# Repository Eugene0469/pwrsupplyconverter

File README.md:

# pwrsupplyconverter

This is a project designing a 220VAC to 28VDC power supply for a jig workstation.View Wiki for more information.

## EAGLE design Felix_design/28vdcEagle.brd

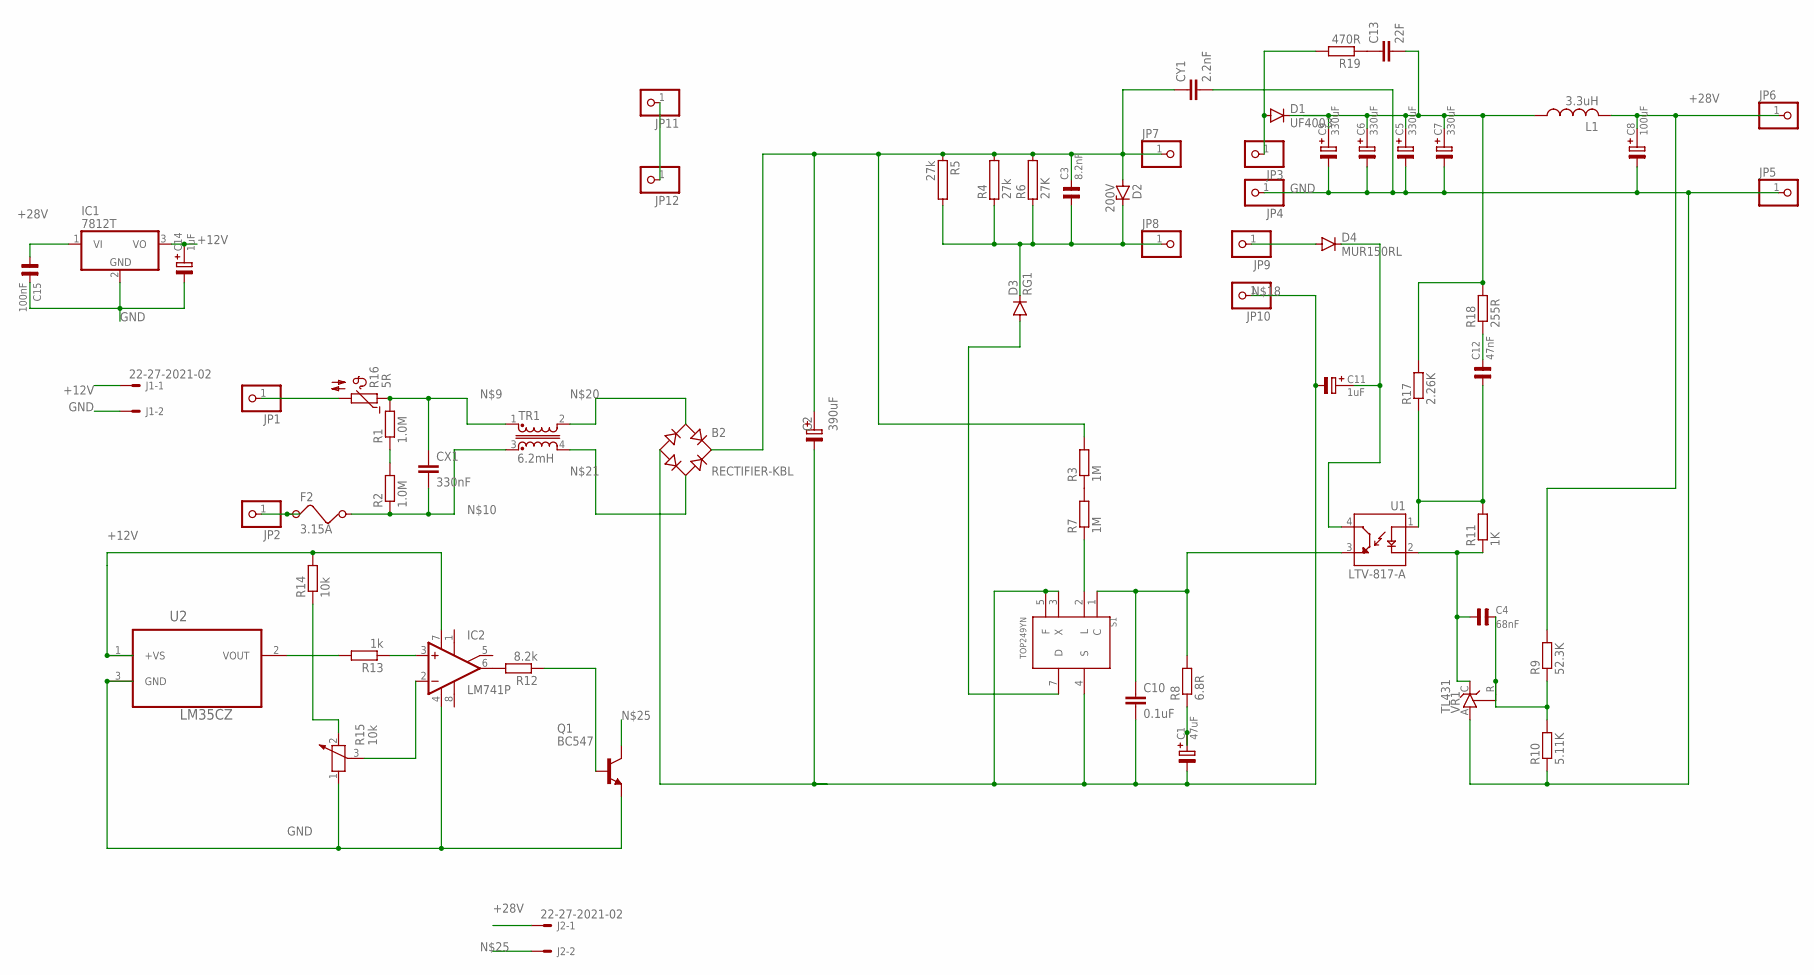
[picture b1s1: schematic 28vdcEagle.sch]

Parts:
B2: RECTIFIER-KBL; KBL
C1: 47uF; E1,0-3
C2: 390uF; E3,5-10
C3: 8.2nF; C14,5
C4: 68nF; C2,5
C5, C6, C7, C9: 330uF; E2,0-5
C8: 100uF; E2,0-5
C10: 0.1uF; C025-030X050
C11, C14: 1uF; E1,0-3
C12: 47nF; C2,5
C13: 22F; C025-030X050
C15: 100nF; C2,5
CX1: 330nF; XC15B10
CY1: 2.2nF; YC7B5
D1: UF4003; DO41-10
D2: 200V; C1702-15
D3: RG1; DO204-10
D4: MUR150RL; DO41-10
F2: 3.15A; FUSE
IC1: 7812T; TO220H
IC2: LM741P; DIL08
J1, J2: 22-27-2021-02; 6410-02
JP1, JP2, JP3, JP4, JP5, JP6, JP7, JP8, JP9, JP10, JP11, JP12: PINHD-1X1; 1X01
L1: 3.3uH; 0207/10
Q1: BC547; TO92
R1, R2: 1.0M; 0207/10
R3, R7: 1M; 0207/10
R4, R5: 27k; KP290
R6: 27K; KP290
R8: 6.8R; 0207/10
R9: 52.3K; 0207/10
R10: 5.11K; 0207/10
R11: 1K; 0207/10
R12: 8.2k; 0207/10
R13: 1k; 0207/10
R14: 10k; 0207/10
R15: 10k; PT-10
R16: 5R; B57164
R17: 2.26K; 0207/10
R18: 255R; 0207/10
R19: 470R; 0207/10
S1: TOP249YN; TO127P470X1029X2061-7P
TR1: 6.2mH; U15
U1: LTV-817-A; DIP762W50P254L510H500Q4
U2: LM35CZ; TO127P254X495-3P
VR1: TL431; TO92-CLP

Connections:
+12V: C14.+, IC1.3 (VO), IC2.7 (V+), J1.1, R14.2, U2.1 (+VS)
+28V: C8.+, C15.1, IC1.1 (VI), J2.1, JP6.1, L1.2, R9.2
GND: C5.-, C6.-, C7.-, C8.-, C9.-, C14.-, C15.2, CY1.2, IC1.2 (GND), IC2.4 (V-), J1.2, JP4.1, JP5.1, Q1.1 (E), R10.1, R15.1, U2.3 (GND), VR1.A
unnamed: R1.1, R2.2
unnamed: B2.+, C2.+, C3.2, CY1.1, D2.A, JP7.1, R3.2, R4.2, R5.1, R6.2
unnamed: C11.+, D4.C, U1.4 (CT)
unnamed: R3.1, R7.2
unnamed: R7.1, S1.2 (L)
unnamed: IC2.6 (OUT), R12.2
unnamed: D3.A, S1.7 (D)
unnamed: C3.1, D2.C, D3.C, JP8.1, R4.1, R5.2, R6.1
unnamed: CX1.1, R1.2, R16.1, TR1.1
unnamed: CX1.2, F2.2, R2.1, TR1.3
unnamed: C4.2, R9.1, R10.2, VR1.R
unnamed: C4.1, R11.1, U1.2 (C), VR1.C
unnamed: C12.1, R11.2, R17.1, U1.1 (A)
unnamed: C5.+, C6.+, C7.+, C9.+, C13.2, D1.C, L1.1, R17.2, R18.2
unnamed: JP11.1, JP12.1
unnamed: C13.1, R19.1
unnamed: C10.1, R8.2, S1.1 (C), U1.3 (ET)
unnamed: B2.-, C1.-, C2.-, C10.2, C11.-, JP10.1, S1.3 (X), S1.4 (S), S1.5 (F)
unnamed: D4.A, JP9.1
unnamed: B2.AC1, TR1.2
unnamed: B2.AC2, TR1.4
unnamed: R13.2, U2.2 (VOUT)
unnamed: Q1.2 (B), R12.1
unnamed: J2.2, Q1.3 (C)
unnamed: IC2.3 (+IN), R13.1
unnamed: JP1.1, R16.2
unnamed: R14.1, R15.2
unnamed: IC2.2 (-IN), R15.3
unnamed: C1.+, R8.1
unnamed: C12.2, R18.1
unnamed: D1.A, JP3.1, R19.2
unnamed: F2.1, JP2.1

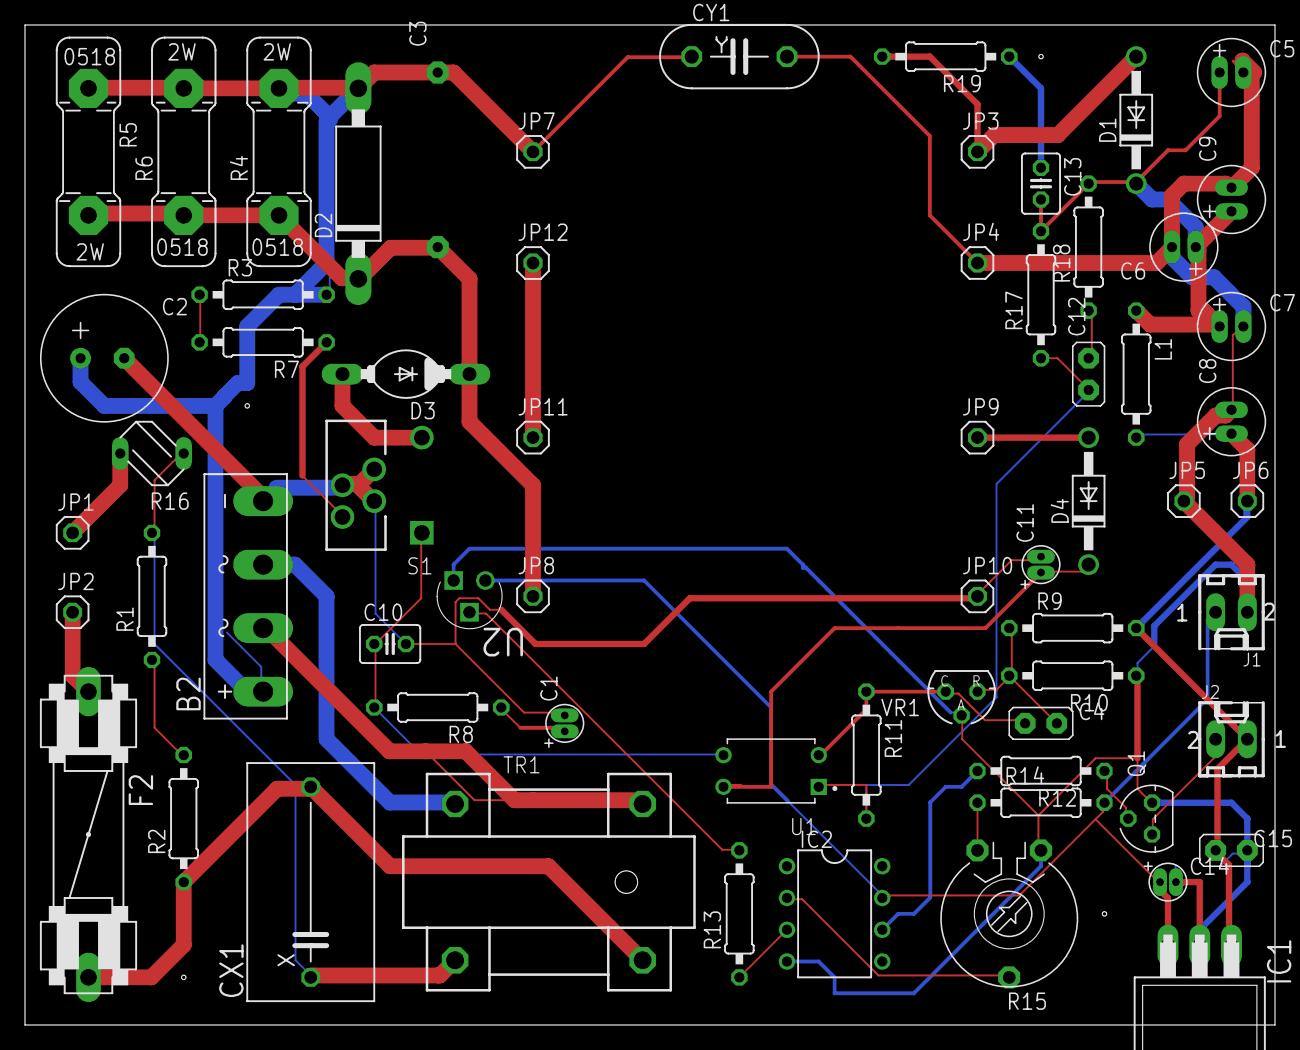
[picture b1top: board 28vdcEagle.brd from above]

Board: 2 copper layers, 100.0 x 80.0 mm, 65 parts (0 on the bottom side), 35 nets.

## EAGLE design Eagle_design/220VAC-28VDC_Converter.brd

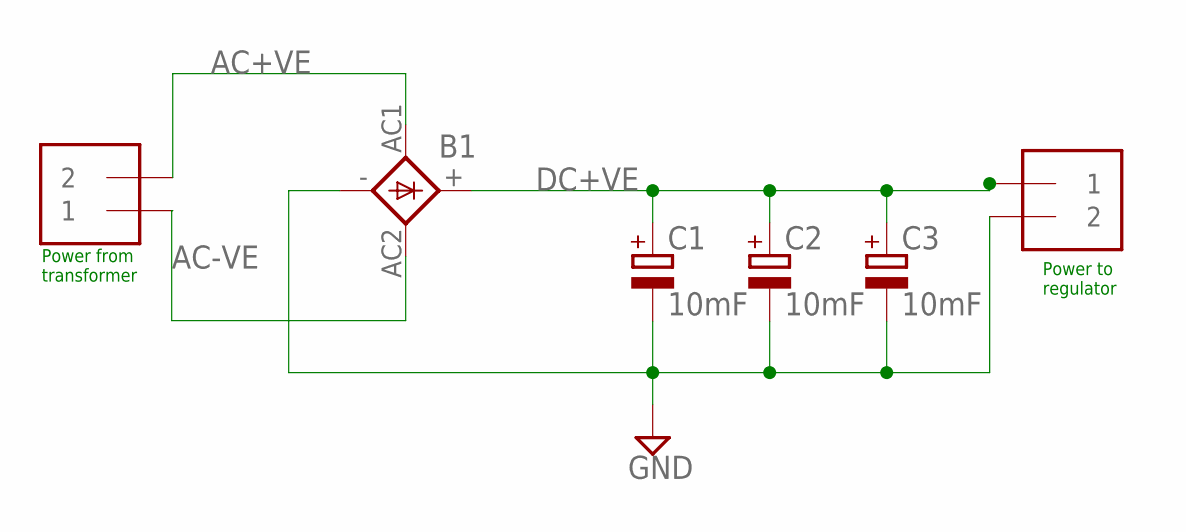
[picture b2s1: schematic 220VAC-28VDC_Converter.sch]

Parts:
B1: KBU
C1, C2, C3: 10mF; EB35D
J1, J2: 1X2-3.5MM

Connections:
AC+VE: B1.AC1, J1.2
AC-VE: B1.AC2, J1.1
DC+VE: B1.+, C1.+, C2.+, C3.+, J2.1
GND: B1.-, C1.-, C2.-, C3.-, J2.2

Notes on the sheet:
Power from transformer
Power to regulator

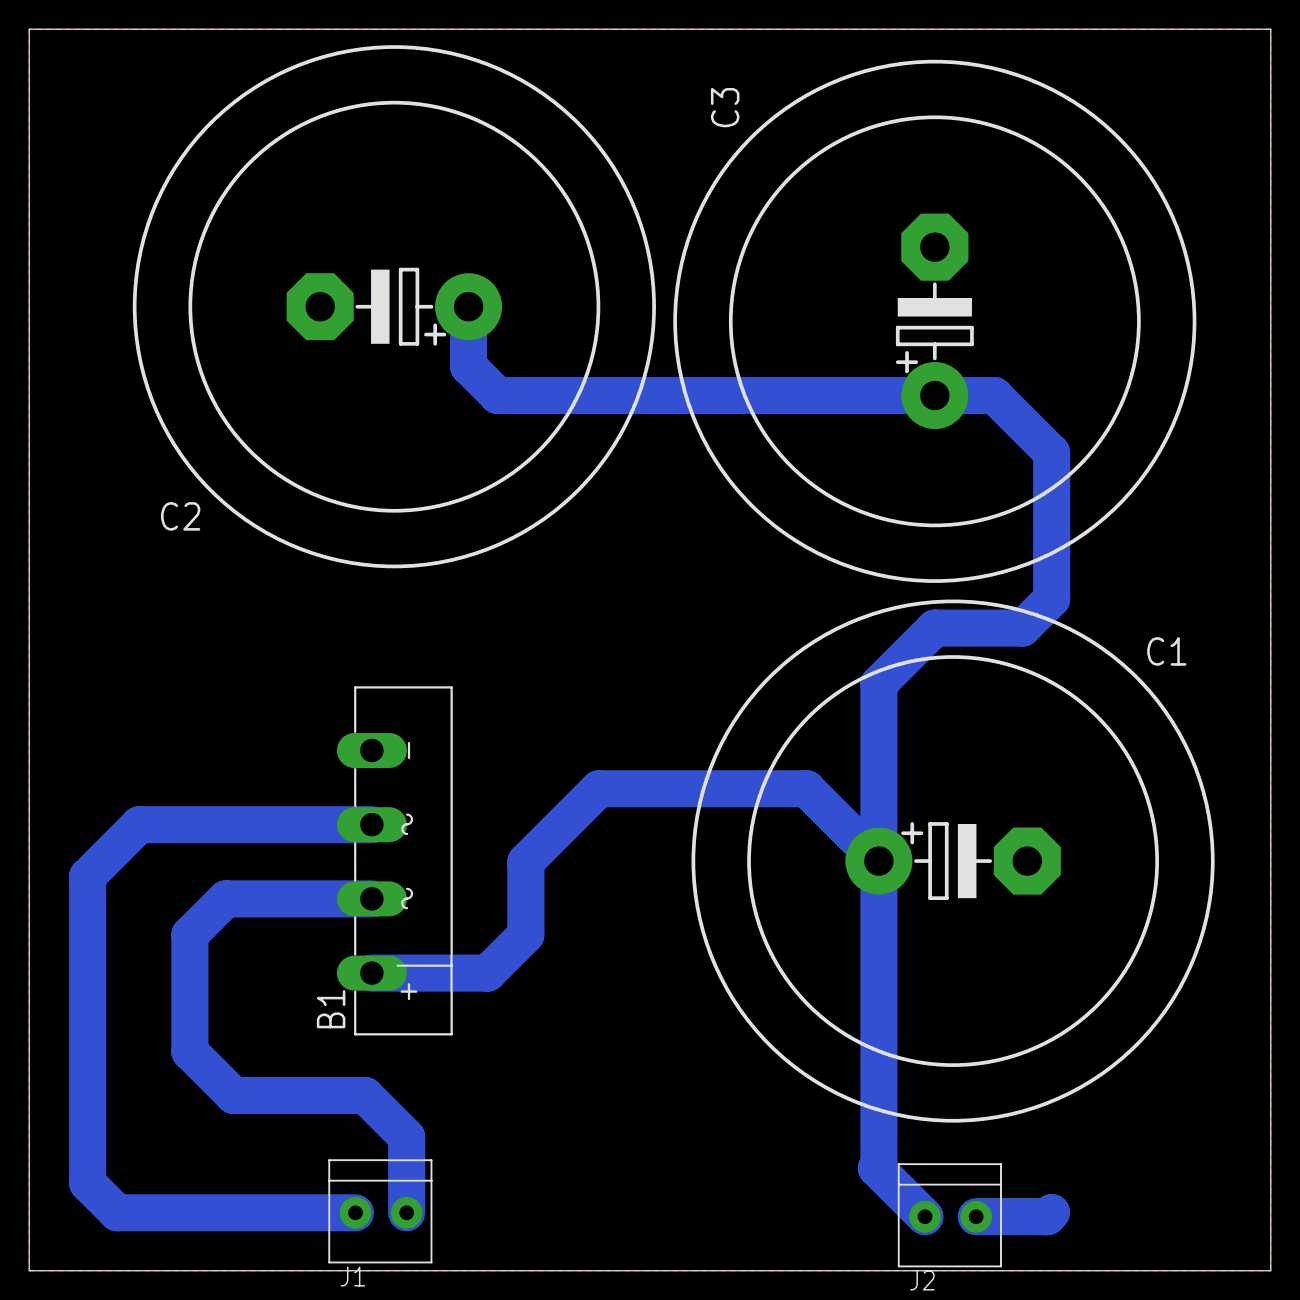
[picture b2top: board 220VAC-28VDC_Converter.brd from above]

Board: 2 copper layers, 85.0 x 85.0 mm, 6 parts (0 on the bottom side), 4 nets.

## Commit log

2020-08-19 Create README.md file
2020-08-19 Create LICENSE file
2020-08-19 Create .gitignore file
2020-08-19 Adds the eagle schematic designs
2020-08-19 Adds PSU simulation file
2020-08-19 Adds proteus design simulation files
2020-08-19 Update README.md to inform of wiki page
2020-08-19 Adds the brd file. This design uses 3 10mF caps in parallel
2020-08-19 Adds labels to the wire connections
2020-08-19 Felix's designs
2020-09-03 Modifies the AC+ve track
2020-09-03 Adds untracked eagle design files
2020-09-03 Completes the proteus design.
    This is after a blank project in master branch.
2020-09-03 Adds untracked files
2020-09-03 Commits changes made in branch develop to branch master
2020-09-03 Deletes duplicated eagle files
2020-09-03 Modifies the parameters in the psu simuation file
2020-09-03 Adds proteus simulation design
